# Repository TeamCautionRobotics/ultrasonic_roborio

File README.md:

# roboRIO breakout for ultrasonic sensors
Designed to connect the roboRIO with the Rockwell 873M series of ultrasonic sensors.

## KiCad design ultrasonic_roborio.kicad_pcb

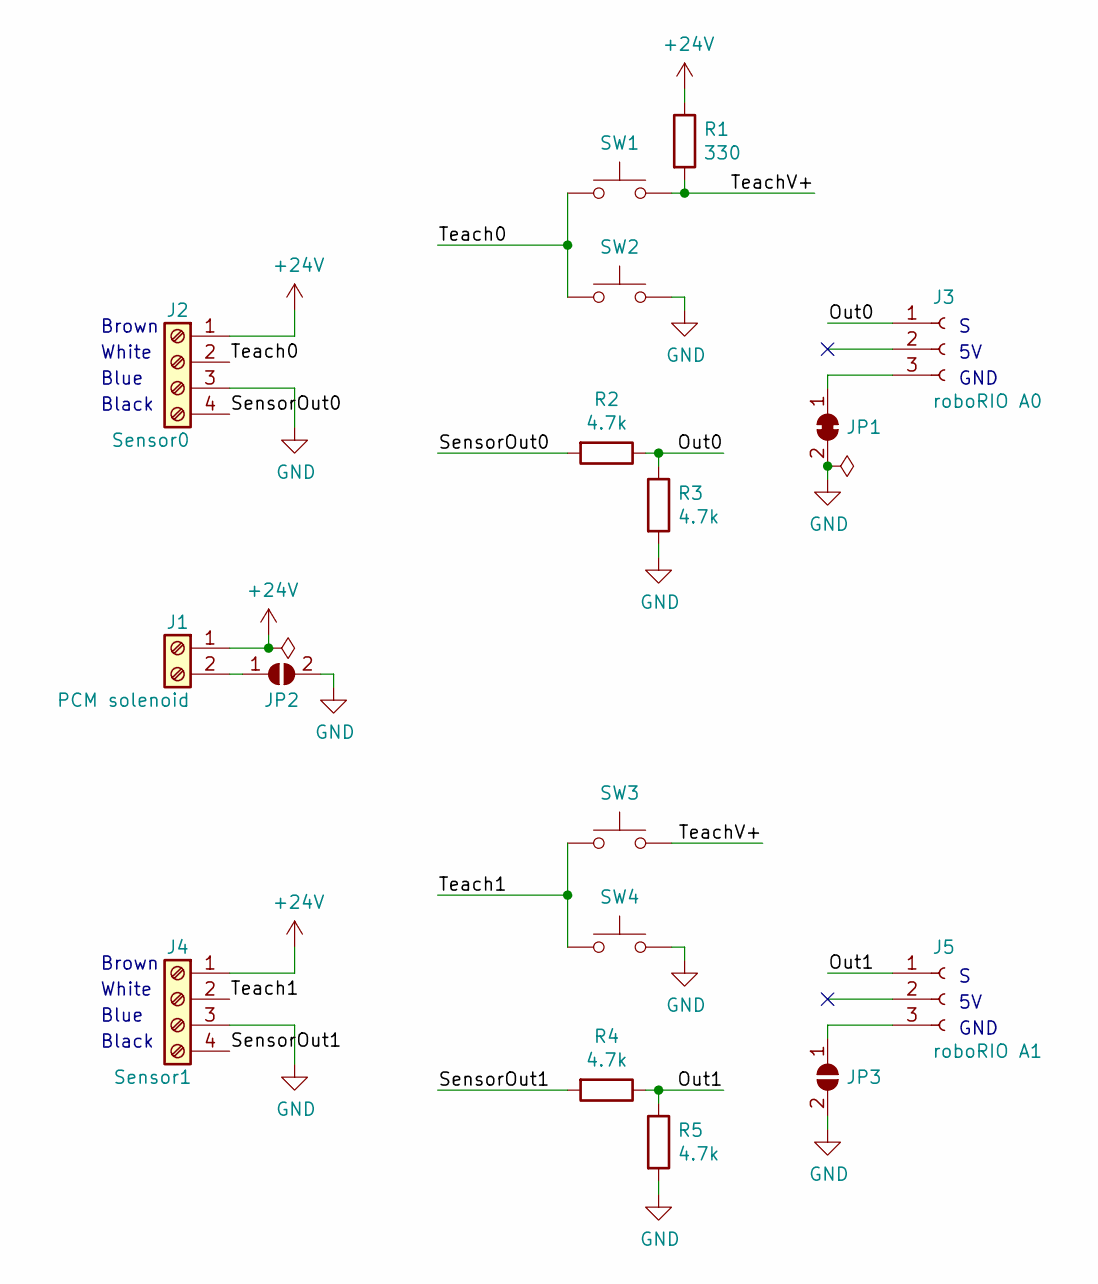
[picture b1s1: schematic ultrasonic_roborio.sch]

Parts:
J1: PCM solenoid; LSF-SMT_3.50_02_135_3.5SN
J2: Sensor0; LSF-SMT_3.50_04_135_3.5SN
J3: roboRIO A0; PinSocket_1x03_P2.54mm_Vertical
J4: Sensor1; LSF-SMT_3.50_04_135_3.5SN
J5: roboRIO A1; PinSocket_1x03_P2.54mm_Vertical
JP1: SolderJumper_2_Bridged; SolderJumper-2_P1.3mm_Bridged_Pad1.0x1.5mm
JP2, JP3: SolderJumper_2_Open; SolderJumper-2_P1.3mm_Open_TrianglePad1.0x1.5mm
R1: 330; R_0603_1608Metric
R2, R3, R4, R5: 4.7k; R_0603_1608Metric
SW1, SW2, SW3, SW4: SW_Push; SW_SPST_PTS810

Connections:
+24V: J1.1, J2.1, J4.1, R1.1
/Out0: J3.1, R2.1, R3.1
/Out1: J5.1, R4.1, R5.1
/SensorOut0: J2.4, R2.2
/SensorOut1: J4.4, R4.2
/Teach0: J2.2, SW1.1, SW2.1
/Teach1: J4.2, SW3.1, SW4.1
/TeachV+: R1.2, SW1.2, SW3.2
GND: J2.3, J4.3, JP1.2 (B), JP2.2 (B), JP3.2 (B), R3.2, R5.2, SW2.2, SW4.2
unnamed: J1.2, JP2.1 (A)
unnamed: J3.3, JP1.1 (A)
unnamed: J5.3, JP3.1 (A)

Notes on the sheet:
Brown
White
Blue
Black
GND

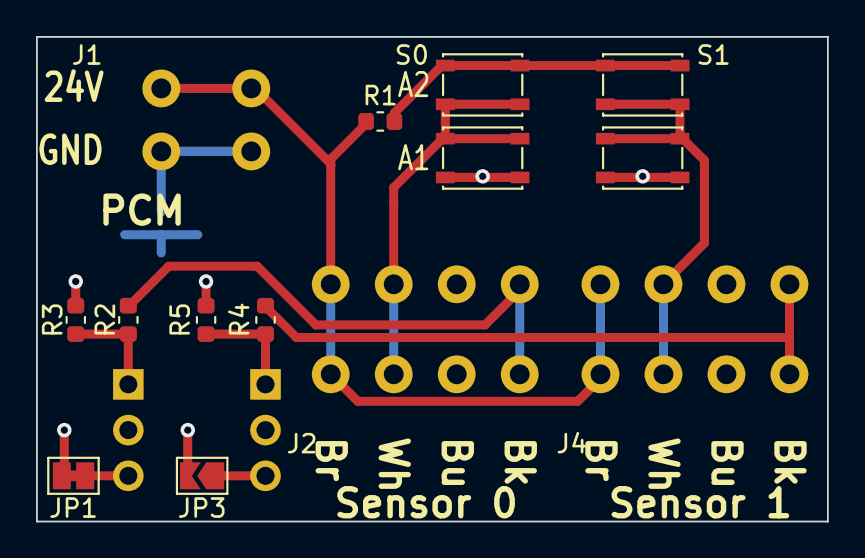
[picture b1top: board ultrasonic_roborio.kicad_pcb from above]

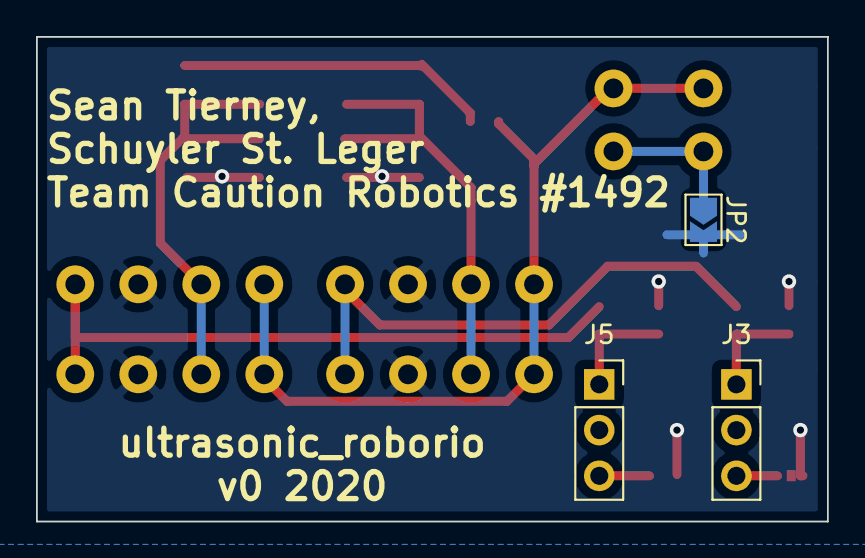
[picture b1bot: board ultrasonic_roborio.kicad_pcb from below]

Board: 2 copper layers, 43.9 x 26.9 mm, 17 parts (3 on the bottom side), 12 nets.

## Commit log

2020-02-23 Add 3D models of Weidmüller terminal blocks This required renaming the footprint libraries to not have spaces. The spaces were invalid characters, but not validated until I opened the footprint prope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
2020-02-24 Switch to smaller switches
2020-02-24 Initial work on tracing
2020-02-25 Finish routing; adjustments to placement
2020-02-25 Finish v0 PCB design Add protection resistor for if A1 and A2 pressed at the same time Change layout to reduce board size Move buttons to not have wires running over them (risk of accidential trigger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
